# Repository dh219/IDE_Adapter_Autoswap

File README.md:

# Auto-byteswitching IDE Adapter for the Atari Falcon

44-pin 2mm pitch IDE host to two device adapter supporting cable select with automatic physical byte swapping

## Atari Falcon

This adapter is intended for use in my Atari Falcon which has an 44-pin 2mm-pitch IDE connection soldered to the board with only one connector for a hard disc.

This allows two discs to be added to the Falcon, if they support running in master/slave configuration, either via jumpers on the discs, or via cable select, which this board supports.

## Byte Swap

This board also automatically swaps data bytes which a suitable hard disc driver on the atari can make use of for faster interoperability with modern machines.

## Youtube

My video demonstrating this and assembing it will be found here

## PCBWay

I have A PCBWay Profile where you may find & order this project when released: https://www.pcbway.com/project/member/?bmbno=2C89C44C-EDF4-43

Copyright 2023 D Henderson, released under the terms of the GPLv2

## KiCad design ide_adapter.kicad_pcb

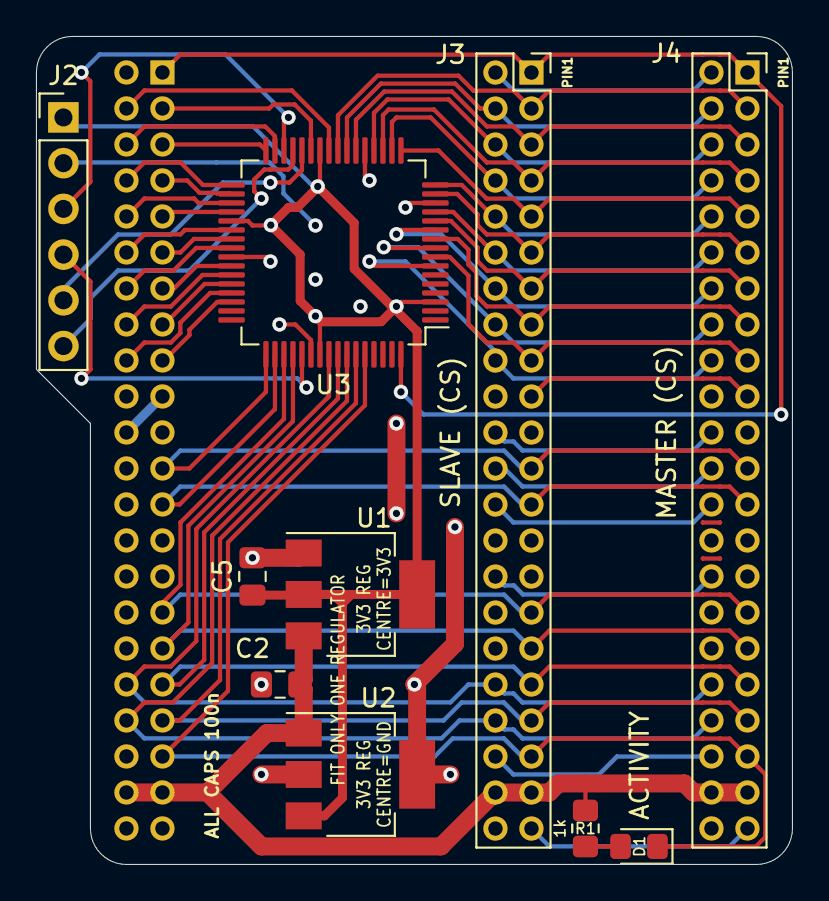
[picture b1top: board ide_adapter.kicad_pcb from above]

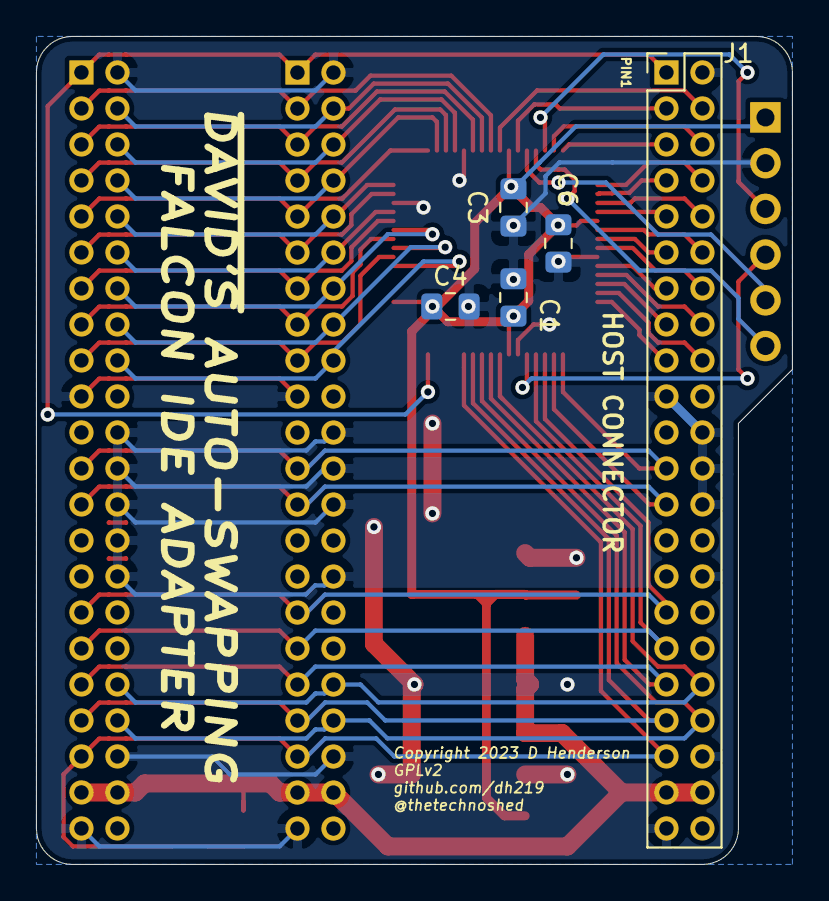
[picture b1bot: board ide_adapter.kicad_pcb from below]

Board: 2 copper layers, 42.0 x 46.0 mm, 15 parts (5 on the bottom side), 50 nets.

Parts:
C1, C2, C3, C4, C5, C6: 100n; C_0805_2012Metric_Pad1.18x1.45mm_HandSolder
D1: LED; LED_0805_2012Metric_Pad1.15x1.40mm_HandSolder
J1: PATA-44_Host; PinHeader_2x22_P2.00mm_Vertical
J2: Conn_01x06_Male; PinHeader_1x06_P2.54mm_Vertical
J3, J4: PATA-44_Drive; PinSocket_2x22_P2.00mm_Vertical
R1: 1k; R_0805_2012Metric_Pad1.20x1.40mm_HandSolder
U1: LM1117-3.3; SOT-223-3_TabPin2
U2: LT1129-3.3_SOT223; SOT-223-3_TabPin2
U3: XC9572XL-VQ64; TQFP-64_10x10mm_P0.5mm

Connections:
+3V3: C1.1, C3.1, C4.1, C5.1, C6.1, J2.1, U1.2, U2.3, U3.3, U3.26, U3.37, U3.55
+5V: C2.1, J1.41, J1.42, J3.41, J3.42, J4.41, J4.42, R1.2, U1.3, U2.1
/D0: J1.17, U3.46
/D1: J1.15, U3.44
/D2: J1.13, U3.42
/D3: J1.11, U3.39
/D4: J1.9, U3.36
/D5: J1.7, U3.34
/D6: J1.5, U3.32
/D7: J1.3, U3.27
/D8: J1.4, U3.25
/D9: J1.6, U3.31
/D10: J1.8, U3.33
/D11: J1.10, U3.35
/D12: J1.12, U3.38
/D13: J1.14, U3.40
/D14: J1.16, U3.43
/D15: J1.18, U3.45
/DA0: J1.35, J3.35, J4.35, U3.57
/DA1: J1.33, J3.33, J4.33, U3.52
/DA2: J1.36, J3.36, J4.36, U3.56
/DD0: J3.17, J4.17, U3.8
/DD1: J3.15, J4.15, U3.10
/DD2: J3.13, J4.13, U3.12
/DD3: J3.11, J4.11, U3.15
/DD4: J3.9, J4.9, U3.17
/DD5: J3.7, J4.7, U3.19
/DD6: J3.5, J4.5, U3.22
/DD7: J3.3, J4.3, U3.24
/DD8: J3.4, J4.4, U3.23
/DD9: J3.6, J4.6, U3.20
/DD10: J3.8, J4.8, U3.18
/DD11: J3.10, J4.10, U3.16
/DD12: J3.12, J4.12, U3.13
/DD13: J3.14, J4.14, U3.11
/DD14: J3.16, J4.16, U3.9
/DD15: J3.18, J4.18, U3.7
/INTRQ: J1.31, J3.31, J4.31, U3.51
/TCK: J2.3, U3.30
/TDI: J2.5, U3.28
/TDO: J2.4, U3.53
/TMS: J2.6, U3.29
/~CS0: J1.37, J3.37, J4.37, U3.59
/~CS1: J1.38, J3.38, J4.38, U3.58
/~DIOR: J1.25, J3.25, J4.25, U3.50
/~DIOW: J1.23, J3.23, J4.23, U3.49
/~LED: D1.1, J1.39, J3.39, J4.39, U3.60
/~RESET: J1.1, J3.1, J4.1, U3.64
GND: C1.2, C2.2, C3.2, C4.2, C5.2, C6.2, J1.2, J1.19, J1.22, J1.24, J1.26, J1.30, J1.40, J1.43, J2.2, J3.2, J3.19, J3.22, J3.24, J3.26, J3.30, J3.40, J3.43, J4.2, J4.19, J4.22, J4.24, J4.26, J4.28, J4.30, J4.40, J4.43, U1.1, U2.2, U3.14, U3.21, U3.41, U3.54
unnamed: D1.2, R1.1

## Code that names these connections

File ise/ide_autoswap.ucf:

#NET "LDS" LOC = "P27" ;
#NET "FC<1>" LOC = "P25" ;

NET D<15> LOC = "P45" ;
NET D<14> LOC = "P43" ;
NET D<13> LOC = "P40" ;
NET D<12> LOC = "P38" ;
NET D<11> LOC = "P35" ;
NET D<10> LOC = "P33" ;
NET D<9> LOC = "P31" ;
NET D<8> LOC = "P25" ;
NET D<7> LOC = "P27" ;
NET D<6> LOC = "P32" ;
NET D<5> LOC = "P34" ;
NET D<4> LOC = "P36" ;
NET D<3> LOC = "P39" ;
NET D<2> LOC = "P42" ;
NET D<1> LOC = "P44" ;
NET D<0> LOC = "P46" ;

NET DD<15> LOC = "P7" ;
NET DD<14> LOC = "P9" ;
NET DD<13> LOC = "P11" ;
NET DD<12> LOC = "P13" ;
NET DD<11> LOC = "P16" ;
NET DD<10> LOC = "P18" ;
NET DD<9> LOC = "P20" ;
NET DD<8> LOC = "P23" ;
NET DD<7> LOC = "P24" ;
NET DD<6> LOC = "P22" ;
NET DD<5> LOC = "P19" ;
NET DD<4> LOC = "P17" ;
NET DD<3> LOC = "P15" ;
NET DD<2> LOC = "P12" ;
NET DD<1> LOC = "P10" ;
NET DD<0> LOC = "P8" ;


NET _CS<1> LOC = "P58" ;
NET _CS<0> LOC = "P59" ;
NET _LED LOC = "P60" ;
NET _RESET LOC = "P64" ;
	
NET _DIOW LOC = "P49" ;
NET _DIOR LOC = "P50" ;
NET INTRQ LOC = "P51" ;

NET DA<0> LOC = "P57" ;
NET DA<1> LOC = "P56" ;
NET DA<2> LOC = "P52" ;

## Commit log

2023-06-21 First attempt at an auto-swapping ide interface.
2023-06-21 Version 1 as ordered
2023-06-30 Initial attempt at decoding commands
2023-07-05 Simplifing the verilog
2023-07-11 Adding silkscreen for release.
2023-07-17 Release firmware added
